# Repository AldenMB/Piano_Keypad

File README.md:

# Piano_Keypad
a small PCB to hook up 12 buttons in a piano configuration.

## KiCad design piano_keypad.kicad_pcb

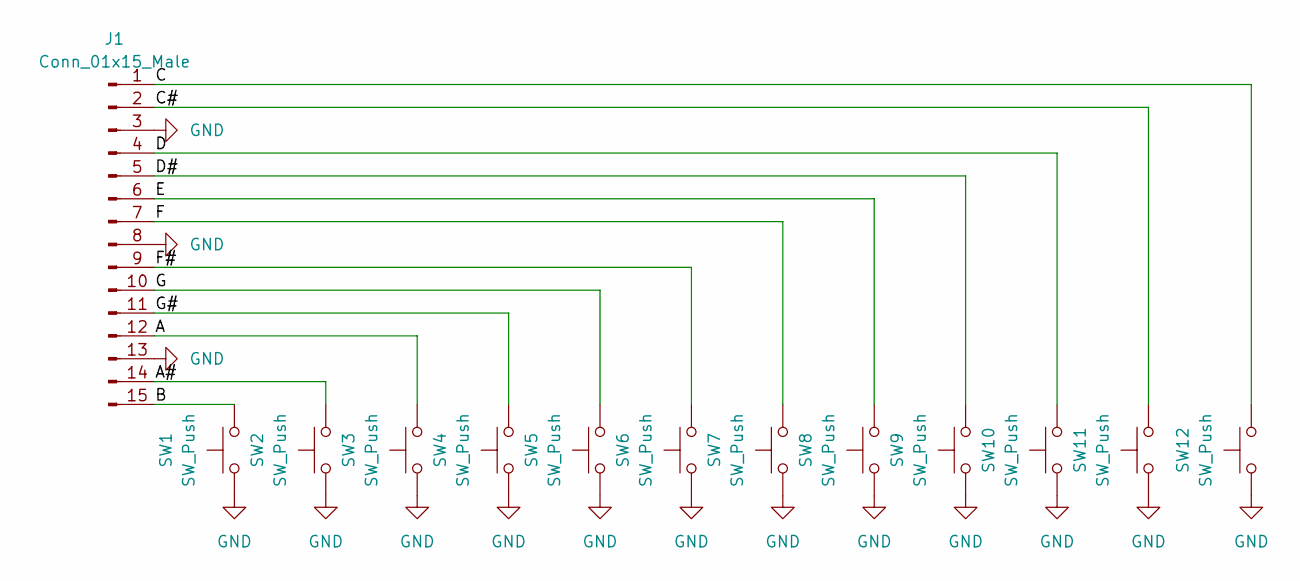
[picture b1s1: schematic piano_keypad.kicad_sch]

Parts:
J1: Conn_01x15_Male; PinHeader_1x15_P2.54mm_Vertical
SW1, SW2, SW3, SW4, SW5, SW6, SW7, SW8, SW9, SW10, SW11, SW12: SW_Push; SW_PUSH_6mm

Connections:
/A: J1.12, SW3.2
/A#: J1.14, SW2.2
/B: J1.15, SW1.2
/C: J1.1, SW12.2
/C#: J1.2, SW11.2
/D: J1.4, SW10.2
/D#: J1.5, SW9.2
/E: J1.6, SW8.2
/F: J1.7, SW7.2
/F#: J1.9, SW6.2
/G: J1.10, SW5.2
/G#: J1.11, SW4.2
GND: J1.3, J1.8, J1.13, SW1.1, SW2.1, SW3.1, SW4.1, SW5.1, SW6.1, SW7.1, SW8.1, SW9.1, SW10.1, SW11.1, SW12.1

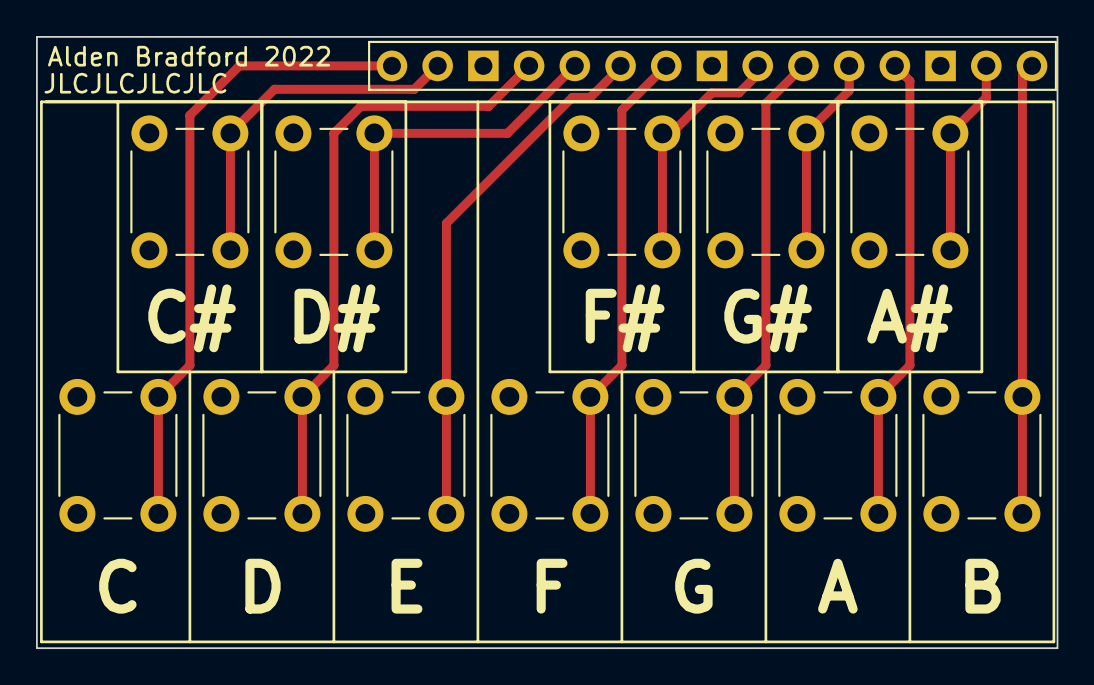
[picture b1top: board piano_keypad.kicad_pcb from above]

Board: 2 copper layers, 56.7 x 34.0 mm, 13 parts (0 on the bottom side), 13 nets.
